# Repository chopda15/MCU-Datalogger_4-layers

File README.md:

# MCU-Datalogger_4-layers
KiCad PCB project - MCU Datalogger 4 layer board

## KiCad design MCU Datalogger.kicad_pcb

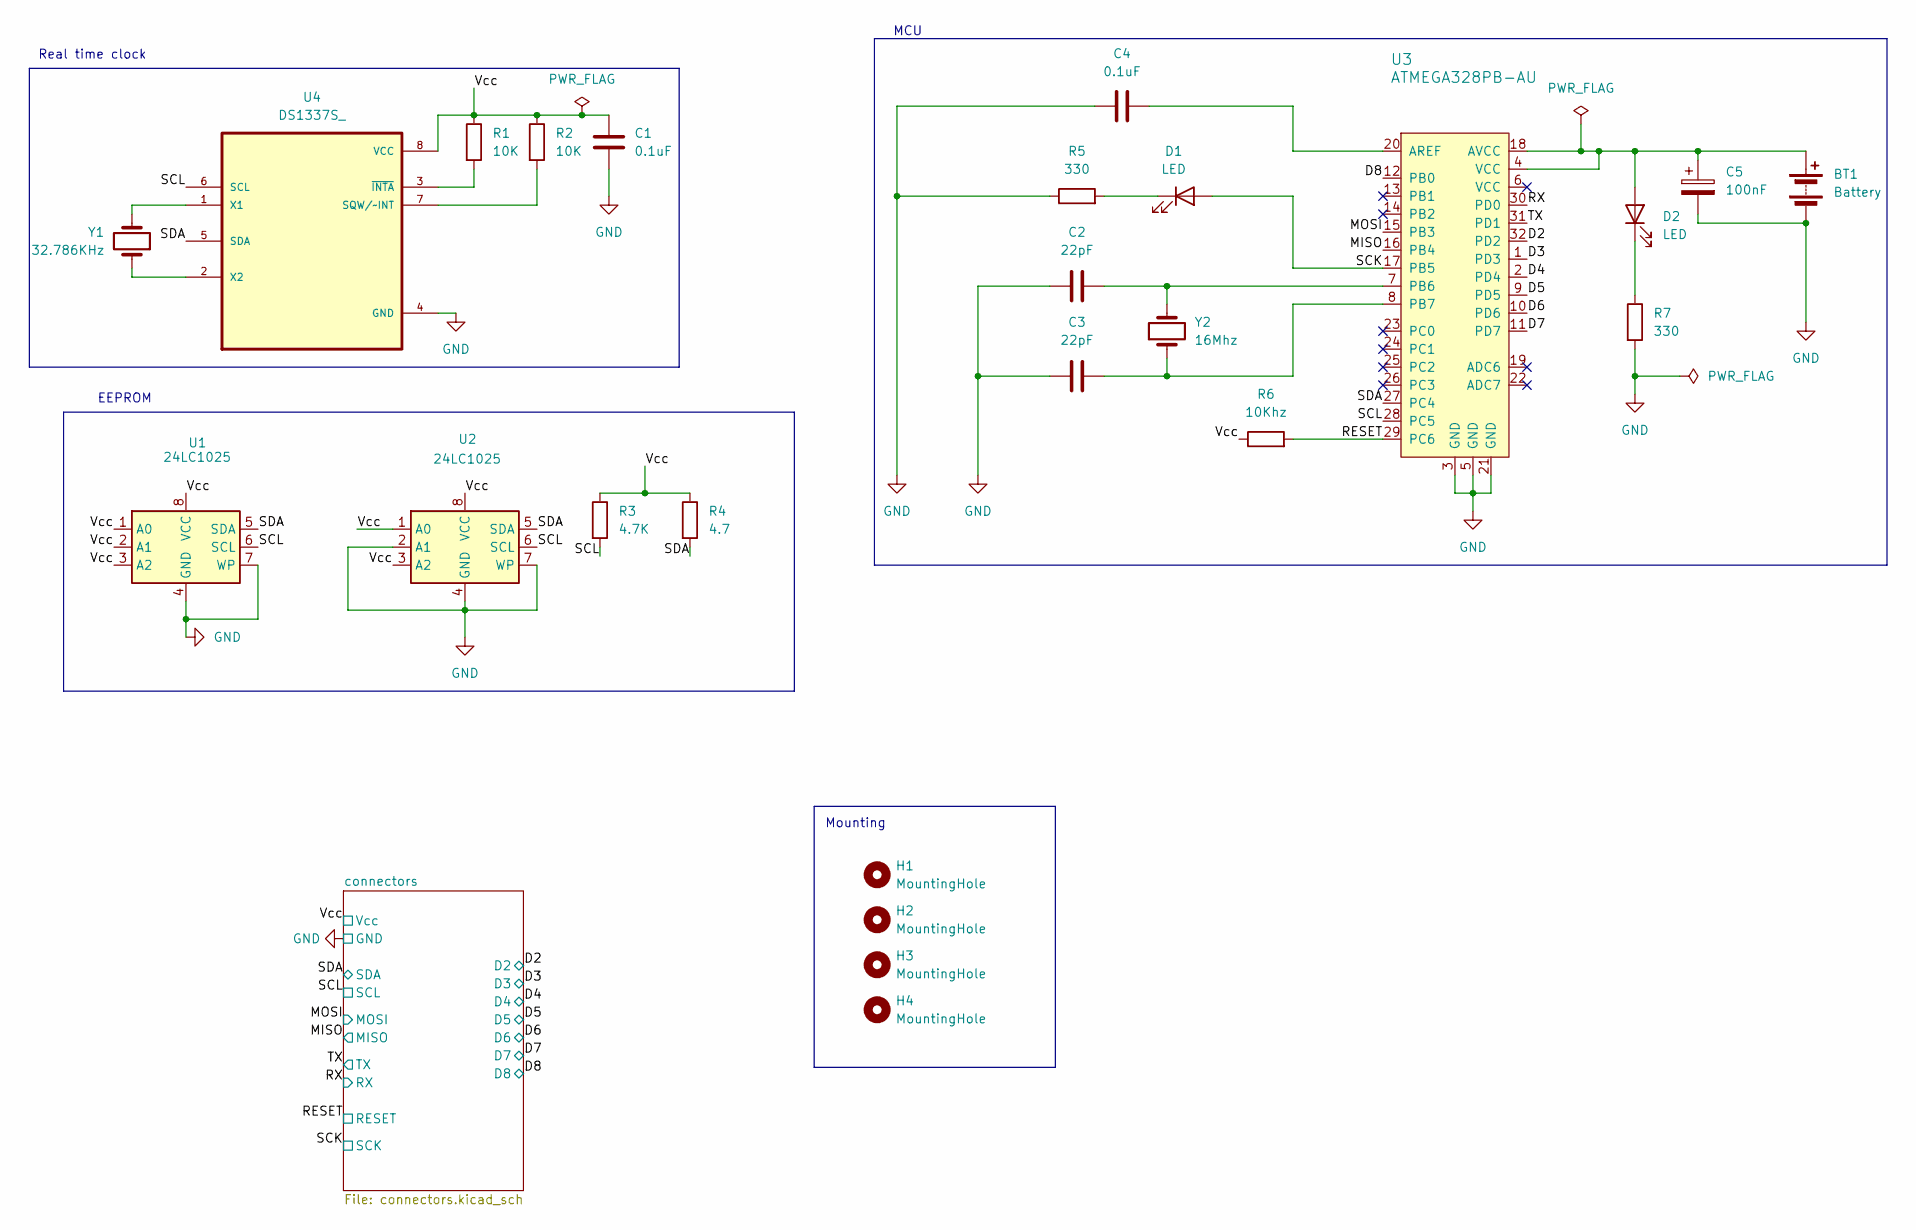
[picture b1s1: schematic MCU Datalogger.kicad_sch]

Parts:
BT1: Battery; PinSocket_1x02_P2.54mm_Vertical
C1, C4: 0.1uF; C_0805_2012Metric
C2, C3: 22pF; C_0805_2012Metric
C5: 100nF; C_0805_2012Metric
D1, D2: LED; LED_0805_2012Metric
H1, H2, H3, H4: MountingHole; MountingHole_2.1mm
R1, R2: 10K; R_0805_2012Metric
R3: 4.7K; R_0805_2012Metric
R4: 4.7; R_0805_2012Metric
R5, R7: 330; R_0805_2012Metric
R6: 10Khz; R_0805_2012Metric
U1, U2: 24LC1025; SOIC-8_3.9x4.9mm_P1.27mm
U3: ATMEGA328PB-AU; TQFP-32_7x7mm; MPN ATMEGA328PB-AU; Digi-Key_PN ATMEGA328PB-AU-ND
U4: DS1337S_; SOIC127P600X175-8N
Y1: 32.786KHz; Crystal_SMD_5032-2Pin_5.0x3.2mm_HandSoldering
Y2: 16Mhz; Crystal_SMD_5032-2Pin_5.0x3.2mm_HandSoldering

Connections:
/D2: U3.32 (PD2); also elsewhere on the board
/D3: U3.1 (PD3); also elsewhere on the board
/D4: U3.2 (PD4); also elsewhere on the board
/D5: U3.9 (PD5); also elsewhere on the board
/D6: U3.10 (PD6); also elsewhere on the board
/D7: U3.11 (PD7); also elsewhere on the board
/D8: U3.12 (PB0); also elsewhere on the board
/MISO: U3.16 (PB4); also elsewhere on the board
/MOSI: U3.15 (PB3); also elsewhere on the board
/RESET: R6.2, U3.29 (PC6); also elsewhere on the board
/RX: U3.30 (PD0); also elsewhere on the board
/SCK: D1.2 (A), U3.17 (PB5)
/SCL: R3.2, U1.6 (SCL), U2.6 (SCL), U3.28 (PC5), U4.6 (SCL); also elsewhere on the board
/SDA: R4.2, U1.5 (SDA), U2.5 (SDA), U3.27 (PC4), U4.5 (SDA); also elsewhere on the board
/TX: U3.31 (PD1); also elsewhere on the board
/Vcc: C1.1, R1.1, R2.1, R3.1, R4.1, R6.1, U1.1 (A0), U1.2 (A1), U1.3 (A2), U1.8 (VCC), U2.1 (A0), U2.3 (A2), U2.8 (VCC), U4.8 (VCC); also elsewhere on the board
GND: BT1.2 (-), C1.2, C2.1, C3.1, C4.1, C5.2, R5.1, R7.2, U1.4 (GND), U1.7 (WP), U2.2 (A1), U2.4 (GND), U2.7 (WP), U3.3 (GND), U3.5 (GND), U3.21 (GND), U4.4 (GND); also elsewhere on the board
unnamed: BT1.1 (+), C5.1, D2.2 (A), U3.4 (VCC), U3.18 (AVCC)
unnamed: D1.1 (K), R5.2
unnamed: D2.1 (K), R7.1
unnamed: C4.2, U3.20 (AREF)
unnamed: C2.2, U3.7 (PB6), Y2.2
unnamed: C3.2, U3.8 (PB7), Y2.1
unnamed: R2.2, U4.7 (SQW/~INT)
unnamed: U4.1 (X1), Y1.2
unnamed: U4.2 (X2), Y1.1
unnamed: R1.2, U4.3 (~INTA)

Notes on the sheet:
MCU
Mounting
Real time clock
EEPROM

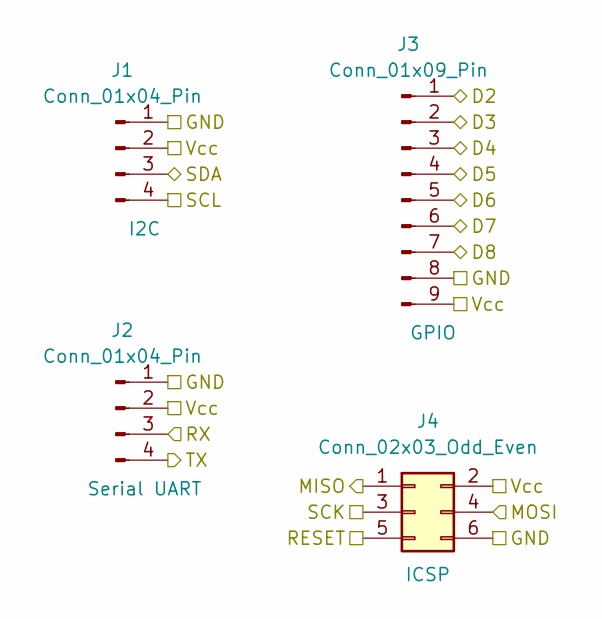
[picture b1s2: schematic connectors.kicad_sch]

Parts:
J1, J2: Conn_01x04_Pin; PinSocket_1x04_P2.54mm_Vertical
J3: Conn_01x09_Pin; PinSocket_1x09_P2.54mm_Vertical
J4: Conn_02x03_Odd_Even; PinSocket_2x03_P2.54mm_Vertical

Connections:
/D2: J3.1; also elsewhere on the board
/D3: J3.2; also elsewhere on the board
/D4: J3.3; also elsewhere on the board
/D5: J3.4; also elsewhere on the board
/D6: J3.5; also elsewhere on the board
/D7: J3.6; also elsewhere on the board
/D8: J3.7; also elsewhere on the board
/MISO: J4.1; also elsewhere on the board
/MOSI: J4.4; also elsewhere on the board
/RESET: J4.5; also elsewhere on the board
/RX: J2.3; also elsewhere on the board
/SCL: J1.4, J4.3; also elsewhere on the board
/SDA: J1.3; also elsewhere on the board
/TX: J2.4; also elsewhere on the board
/Vcc: J1.2, J2.2, J3.9, J4.2; also elsewhere on the board
GND: J1.1, J2.1, J3.8, J4.6; also elsewhere on the board

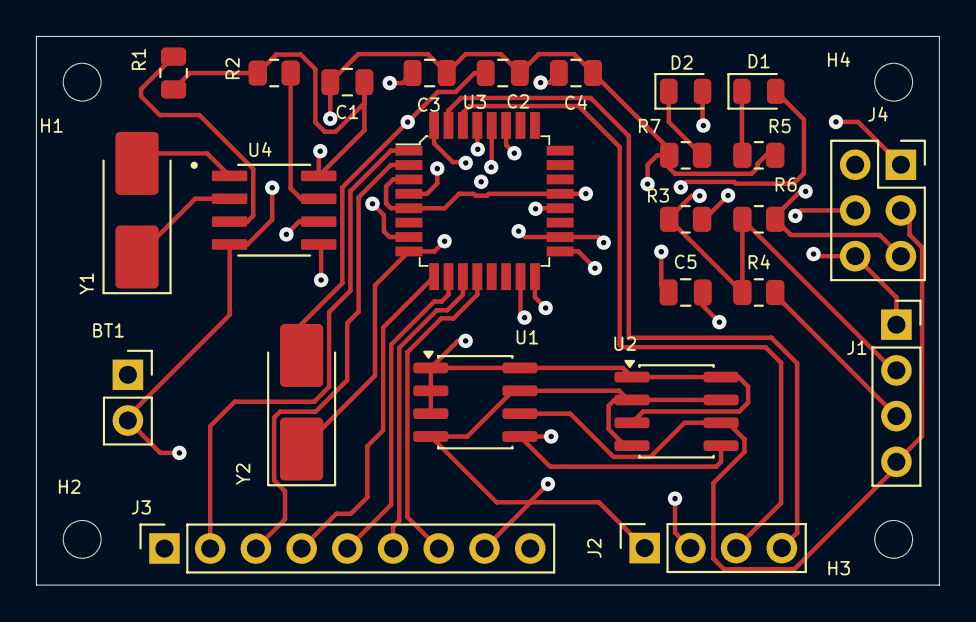
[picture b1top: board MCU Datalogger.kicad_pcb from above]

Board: 4 copper layers, 50.2 x 30.5 mm, 29 parts (0 on the bottom side), 27 nets.

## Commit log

2026-06-08 Initial commit: add project files and .gitignore
2026-06-08 Clear README
